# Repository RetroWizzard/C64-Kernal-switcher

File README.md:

# C64-Kernal-switcher
A switchless C64 kernal switcher

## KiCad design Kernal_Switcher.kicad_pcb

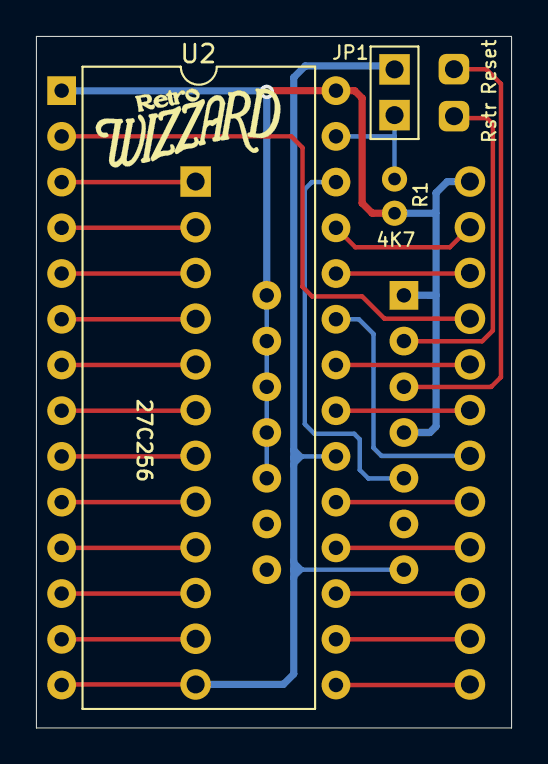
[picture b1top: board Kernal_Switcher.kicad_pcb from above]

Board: 2 copper layers, 26.4 x 38.4 mm, 8 parts (1 on the bottom side), 28 nets.

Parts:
J1: Conn_01x12; PinHeader_1x12_P2.54mm_Vertical_1-12_naked
J2: Conn_01x12_13-24; PinHeader_1x12_P2.54mm_Vertical_13-24_naked
JP1: JP_2_Open; PinHeader_1x02_P2.54mm_Vertical_custom
R1: R; R_Axial_DIN0204_L3.6mm_D1.6mm_P1.90mm_Vertical
Reset: Conn_01x01; PinHeader_1x01_P2.54mm_Vertical_naked
Rstr: Conn_01x01; PinHeader_1x01_P2.54mm_Vertical_naked
U1: 74HC74; DIP-14_W7.62mm_custom
U2: 27C256; DIP-28_W15.24mm

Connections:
/A0: J1.8, U2.10
/A1: J1.7, U2.9
/A2: J1.6, U2.8
/A3: J1.5, U2.7
/A4: J1.4, U2.6
/A5: J1.3, U2.5
/A6: J1.2, U2.4
/A7: J1.1, U2.3
/A8: J2.23, U2.25
/A9: J2.22, U2.24
/A10: J2.19, U2.21
/A11: J2.18, U2.23
/A12: J2.21, U2.2
/A13: U1.5, U2.26
/D0: J1.9, U2.11
/D1: J1.10, U2.12
/D2: J1.11, U2.13
/D3: J2.13, U2.15
/D4: J2.14, U2.16
/D5: J2.15, U2.17
/D6: J2.16, U2.18
/D7: J2.17, U2.19
/GND: J1.12, JP1.1, U1.7, U2.14, U2.20
/OE: J2.20, U2.22
/RESET: Reset.1, U1.3
/RESTORE: Rstr.1, U1.2
/VCC: J2.24, R1.2, U1.1, U1.4, U1.10, U1.11, U1.12, U1.13, U1.14, U2.1, U2.28
unnamed: JP1.2, R1.1, U2.27
